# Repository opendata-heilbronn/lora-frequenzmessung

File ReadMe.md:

# LoRa Crowd Density Measurement

> Measure crowd density in public spaces using BLE scanning on ESP32 sensors, transmitted via LoRaWAN (TTN), stored in TimescaleDB, and visualised in a web UI and Grafana.

---

> **Canonical repository:** https://codeberg.org/cfhn/lora-frequenzmessung
>
> Mirrors exist on GitHub and GitLab for visibility, but they are read-only.
> **Contributions, issues, and pull requests belong on Codeberg.**

---

## Introduction

This project provides an end-to-end system for measuring crowd density in public spaces. Small ESP32-based sensors scan for nearby Bluetooth devices and transmit a count over LoRaWAN via The Things Network. A backend stack ingests the data and makes it available for real-time dashboards.

**Data flow:**

```
ESP32 (BLE scan)
    └─ LoRaWAN (TTN) ─→ MQTT Broker
                              └─ Aggregator ─→ Backend API ─→ TimescaleDB
                                                                    └─→ Grafana
                                                                    └─→ Web UI (via ManagementAPI)
```

**Maintained by** [Code for Heilbronn (CFHN)](https://codeforheilbronn.de/).

---

## Architecture

### Component Overview

| Service        | Language   | Port  | Purpose                                              |
|----------------|------------|-------|------------------------------------------------------|
| Backend        | Go/Fiber   | 3001  | Internal sensor CRUD + data ingestion (X-Internal-Key protected) |
| ManagementAPI  | Go/Fiber   | 3002  | Public API: JWT auth, TTN registration, firmware builds |
| Aggregator     | Go         | —     | MQTT subscriber → forwards data to Backend           |
| Frontend       | Vue 3/Vite | 5173  | Management web UI                                    |
| TimescaleDB    | PostgreSQL | 5432  | Time-series sensor data storage                      |
| Mosquitto      | MQTT       | 1883  | Message broker (TTN bridge)                          |
| Grafana        | —          | 3000  | Dashboard / visualisation                            |

### Request Paths

```
Browser  ──→  Frontend (Vite, :5173)
                  └─ /api/*  ──→  ManagementAPI (:3002)  ──→  Backend (:3001)
                  └─ /auth/* ──→  ManagementAPI (:3002)

TTN      ──→  MQTT (:1883)
                  └─  Aggregator  ──→  Backend (:3001)  ──→  TimescaleDB
```

<!-- Screenshots / diagrams can be added here once available -->

---

## Hardware Requirements

- **Heltec WiFi LoRa 32 V3** (ESP32-S3) — one per measurement location
- A LoRaWAN gateway in range
- A [The Things Network](https://www.thethingsnetwork.org/) application
- A server to run the backend stack (Docker + Docker Compose)

---

## Getting Started

### Prerequisites

| Tool | Version |
|------|---------|
| Go | 1.24+ |
| Node.js | 18+ |
| Docker & Docker Compose | latest |
| PlatformIO CLI | latest (for firmware builds) |
| `golang-migrate` | latest |

Install `golang-migrate` (macOS):

```bash
brew install golang-migrate
```

### Quick Start (Development)

```bash
# 1. Clone
git clone https://codeberg.org/cfhn/lora-frequenzmessung.git
cd lora-frequenzmessung

# 2. Configure environment
cp .env.local.dist backend/.env
# Edit backend/.env and fill in all required values (see Environment Variables below)

# 3. Start infrastructure (TimescaleDB, Mosquitto, Grafana)
make infra

# 4. Run database migrations
migrate -database "$DB_DSN" -path db/migrations up

# 5. Start all services in parallel
make dev
```

`make dev` starts the Backend (`:3001`), ManagementAPI (`:3002`), Aggregator, and Frontend (`:5173`) in parallel.

### Environment Variables

Copy `.env.local.dist` to `backend/.env` and fill in the required values.

| Variable | Required | Service(s) | Description |
|---|---|---|---|
| `DB_DSN` | Yes | Backend | PostgreSQL connection string |
| `INTERNAL_API_KEY` | Yes | Backend, ManagementAPI, Aggregator | Shared secret for internal service auth |
| `BACKEND_INTERNAL_URL` | Yes | ManagementAPI, Aggregator | URL of the internal Backend API (e.g. `http://localhost:3001`) |
| `JWT_SECRET` | Yes | ManagementAPI | HS256 signing key — min 32 characters |
| `ADMIN_USERNAME` | Yes | ManagementAPI | Admin login username |
| `ADMIN_PASSWORD` | Yes | ManagementAPI | Admin login password |
| `BROKER_HOST` | Yes | Aggregator | MQTT broker hostname |
| `BROKER_PORT` | Yes | Aggregator | MQTT broker port (usually `1883`) |
| `MQTT_USERNAME` | Yes | Aggregator | MQTT username (TTN app ID + `@ttn`) |
| `MQTT_PASSWORD` | Yes | Aggregator | MQTT API key from TTN |
| `TOPIC` | Yes | Aggregator | TTN MQTT topic to subscribe to |
| `TTN_APP_ID` | No | ManagementAPI | TTN application ID (for device provisioning) |
| `TTN_API_KEY` | No | ManagementAPI | TTN API key (for device provisioning) |
| `SENSOR_PAX_PATH` | No | ManagementAPI | Path to firmware source directory (default: `./sensor-pax`) |
| `CORS_ORIGINS` | No | ManagementAPI | Comma-separated allowed origins (e.g. `http://localhost:5173`) |

---

## Development Commands

All commands are run from the repository root via `make`. Run `make help` to see the full list.

```bash
make help              # Show all available targets

# Infrastructure
make infra             # Start TimescaleDB, Mosquitto, Grafana
make infra-down        # Stop infrastructure containers

# Backend services (each in its own terminal, or use make dev)
make backend           # Run internal Backend API (port 3001)
make management        # Run ManagementAPI (port 3002)
make aggregator        # Run MQTT Aggregator

# Frontend
make frontend          # Run Vite dev server (port 5173)

# All services at once
make dev               # Start infra + all services in parallel

# Testing
make test              # Run all Go tests
make test-frontend     # Run Playwright unit tests (mocked, no backend needed)
make test-frontend-live # Run Playwright integration tests (needs running backend)

# Build
make build             # Build all Go binaries + frontend bundle
```

---

## Testing

### Go Tests

```bash
cd backend
go test ./...
```

### Frontend — Playwright

There are two test projects configured in `frontend/playwright.config.ts`:

| Project | Command | Requires backend? |
|---|---|---|
| `unit` | `make test-frontend` | No (uses mocked API) |
| `integration` | `make test-frontend-live` | Yes (hits real backend) |

Run a single spec:

```bash
cd frontend
npx playwright test e2e/add-sensor.spec.ts
```

---

## Production Deployment

Docker images are published to `codeberg.org/cfhn/lora-frequenzmessung/<service>`.

Use `docker-compose-deploy.yml` to deploy the full stack:

```bash
docker compose -f docker-compose-deploy.yml up -d
```

All environment variables listed in the table above must be set in the production environment. For `POSTGRES_PASSWORD` and `GF_ADMIN_PASSWORD`, **change the defaults** — the development defaults (`password` / `admin`) are insecure.

---

## Project Structure

```
lora-frequenzmessung/
├── backend/               # All Go source code (single go.mod)
│   ├── Backend/           # Internal HTTP API (port 3001)
│   ├── ManagementAPI/     # Public JWT API (port 3002)
│   ├── Aggregator/        # MQTT subscriber
│   ├── structs/           # Shared Go types
│   └── internal/          # Shared internal packages
├── frontend/              # Vue 3 + Vite management UI
│   └── e2e/               # Playwright tests
├── sensor-pax/            # ESP32 firmware (PlatformIO / libpax)
├── db/
│   └── migrations/        # SQL migrations (golang-migrate)
├── docker/                # Dockerfiles + service configs
├── docs/                  # Additional documentation
├── hardware/              # Hardware schematics / notes
├── docker-compose.yml     # Development infrastructure
├── docker-compose-deploy.yml # Production deployment
└── Makefile               # Developer shortcuts
```

---

## Contributing

Contributions are welcome! This project is maintained by volunteers at [Code for Heilbronn (CFHN)](https://codeforheilbronn.de/).

**All contributions go through Codeberg:**

1. Fork the repository on [Codeberg](https://codeberg.org/cfhn/lora-frequenzmessung)
2. Create a feature branch (`git checkout -b feature/my-feature`)
3. Commit your changes following the existing code style
4. Open a pull request on Codeberg

Please open an issue first for larger changes so we can discuss the approach.

---

## License

MIT © 2026 [Open Data Heilbronn](https://codeforheilbronn.de/)

See [LICENSE](LICENSE) for the full text.

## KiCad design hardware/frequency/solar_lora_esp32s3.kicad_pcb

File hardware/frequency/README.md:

# Solar LoRa ESP32-S3 — Custom Slim Board

**Version:** 1.0
**Date:** 2026-02-15
**Band:** 868 MHz (EU)
**Based on:** Heltec WiFi LoRa 32 V3 (redesigned, no OLED)

---

## Overview

A slim, solar-powered LoRa development board built around the ESP32-S3-MINI-1
and Semtech SX1262. Designed for low-power outdoor sensor nodes.

**Board dimensions:** 22.0mm x 58.0mm (2-layer, 1.6mm thick, rounded corners)

## Key Features

- **ESP32-S3-MINI-1-N8** — WiFi + BLE, 8MB flash, native USB (no CH340 needed)
- **SX1262** — LoRa transceiver, 868 MHz, +22 dBm TX power, ultra-low sleep
- **CN3065** — Solar LiPo charger with Schottky diode OR from USB/solar
- **AP2112K-3.3** — 3.3V LDO, 600mA, ~55µA quiescent current
- **No OLED** — power saved for battery/solar operation
- **Battery monitoring** — voltage divider on ADC1 (GPIO1)
- **USB-C** — charging + native USB programming (no UART bridge chip)

## Pin Mapping (Software-Compatible with Heltec V3)

| Function      | ESP32-S3 GPIO | Notes                    |
|---------------|---------------|--------------------------|
| LoRa SCK      | GPIO8         | SPI clock                |
| LoRa MOSI     | GPIO9         | SPI data out             |
| LoRa MISO     | GPIO10        | SPI data in              |
| LoRa CS       | GPIO11        | SPI chip select          |
| LoRa RST      | GPIO12        | SX1262 reset             |
| LoRa BUSY     | GPIO13        | SX1262 busy flag         |
| LoRa DIO1     | GPIO14        | SX1262 interrupt         |
| USB D-        | GPIO19        | Native USB               |
| USB D+        | GPIO20        | Native USB               |
| Battery ADC   | GPIO1         | Via 100k/100k divider    |
| LED           | GPIO35        | User status LED (green)  |
| BOOT          | GPIO0         | Boot button (pull-up)    |
| RESET         | EN            | Reset button (pull-up)   |

## Power Architecture

```
USB-C (5V) ──D1 (SS14)──┐
                          ├── VOR ──► CN3065 ──► VBAT ──► AP2112K ──► +3V3
Solar (5-6V) ─D2 (SS14)─┘            │
                                ┌─────┘
                                │
                            JST-PH (LiPo 3.7V)
```

- **Solar panel recommendation:** 5V-6V, 500mA+ (e.g., 6V/1W mini panel)
- **Battery:** Single-cell LiPo, JST-PH 2-pin, 500mAh–2000mAh
- **Charge current:** Set by R1 (3kΩ → ~400mA). Adjust per CN3065 datasheet.
- **Charge indicator:** LED1 (red) on CHRG pin

## RF Design Notes (CRITICAL for 868 MHz performance)

The SX1262 RF section uses the Semtech AN1200.39 reference matching network:

```
SX1262 RFO ── C11 (1.0pF) ──┬── L2 (3.9nH) ── GND
                              │
                              ├── C12 (1.5pF) ── GND
                              │
                              └── SMA Antenna Connector
```

**Layout rules:**
1. RF trace from RFO to SMA MUST be 50Ω impedance matched
   - For standard 1.6mm FR4 (εr=4.5), use ~0.7mm trace on top layer with
     continuous ground plane beneath → microstrip ~50Ω
2. Keep RF traces as short as possible (< 15mm ideal)
3. NO vias in the RF signal path
4. Solid ground plane under entire SX1262 and RF section (back copper)
5. Multiple GND vias around SX1262 exposed pad
6. Place matching components (C11, L2, C12) directly adjacent to RFO pin
7. Keep >2mm clearance between RF trace and any other signal traces
8. SX1262 DC-DC inductor (L1, 15nH) must be close to VR_PA/VDD_IN pins

## TCXO

The 32 MHz TCXO (Y1) provides the reference clock for SX1262.
DIO3 of SX1262 can be configured in software to power the TCXO
(saves power in deep sleep). Connect TCXO VDD to SX1262 DIO3 output
if desired, or to +3V3 for always-on operation.

## How to Complete and Order

### Step 1: Open in KiCad 7+
- Open `solar_lora_esp32s3.kicad_pro`
- Review schematic (`.kicad_sch`) — check net connections
- Review PCB layout (`.kicad_pcb`) — components are placed but NOT routed

### Step 2: Route the PCB
- Use KiCad's interactive router (press 'X' to route)
- Route power traces first (+3V3, VBAT, GND) with wider widths (0.3-0.5mm)
- Route SPI bus (0.2mm traces, keep parallel, similar length)
- Route RF trace LAST — use 50Ω microstrip (see RF notes above)
- Fill ground zones (Edit → Fill All Zones, or press 'B')
- Run DRC (Inspect → Design Rules Check)

### Step 3: Generate Gerbers
- File → Fabrication Outputs → Gerbers
- Select layers: F.Cu, B.Cu, F.SilkS, B.SilkS, F.Mask, B.Mask, Edge.Cuts
- Also generate drill files (Excellon format)

### Step 4: Order from JLCPCB
- Go to jlcpcb.com → Order Now
- Upload Gerber ZIP
- Settings: 2-layer, 1.6mm, FR4, HASL lead-free
- For assembly: upload `BOM_JLCPCB.csv` and `CPL_JLCPCB.csv`
- Select "Economic PCBA" for cost savings
- Review component placement in the JLCPCB viewer

### Step 5: Verify LCSC Part Availability
Some parts (ESP32-S3-MINI-1, SX1262) may be "Extended" parts on JLCPCB
(extra $3 fee per unique extended part). Check availability before ordering.

## LCSC Part Alternatives

| Component | Primary LCSC | Alternative LCSC | Notes |
|-----------|-------------|-----------------|-------|
| ESP32-S3-MINI-1-N8 | C2913206 | C3013847 (N4 variant) | N4 = 4MB flash |
| SX1262IMLTRT | C125702 | C2843fault | Check stock |
| CN3065 | C82081 | C264872 | Same IC, different mfg |
| AP2112K-3.3 | C51118 | C166012 | Same specs |

## Low Power Tips

1. Use ESP32-S3 deep sleep (~7µA) between LoRa transmissions
2. Configure SX1262 sleep mode after TX/RX (~600nA)
3. TCXO powered by DIO3 (auto-off in sleep)
4. No OLED = ~15mA saved
5. AP2112K quiescent: ~55µA (consider ME6211 for ~40µA)
6. Total deep sleep: ~10-15µA (board level)
7. With 1000mAh battery + 6V/1W solar: indefinite outdoor operation

## Software

Compatible with:
- **Arduino IDE** — Use Heltec ESP32 board package, select "WiFi LoRa 32 V3"
- **PlatformIO** — board = `heltec_wifi_lora_32_V3`
- **ESP-IDF** — Target ESP32-S3, configure SPI pins manually
- **RadioLib** — SX1262 library, use pin definitions from table above

Example Arduino setup:
```cpp
#include <RadioLib.h>
SX1262 radio = new Module(11, 14, 12, 13); // CS, DIO1, RST, BUSY
// SPI: SCK=8, MOSI=9, MISO=10
```

## Development Setup

### Prerequisites

- Go 1.21+
- Node.js 18+
- Docker & Docker Compose
- [golang-migrate](https://github.com/golang-migrate/migrate) CLI

### Start Infrastructure

```bash
docker-compose up -d   # TimescaleDB, Mosquitto, Grafana
migrate -database "$DB_DSN" -path db/migrations up
```

### Start the Backend

```bash
cd backend
cp ../.env.local.dist .env.local   # adjust DB_DSN, TTN keys etc.
source .env.local
go run ./Backend
```

The API server starts on **port 3001**.

### Start the Frontend

```bash
cd frontend
npm install
npm run dev
```

The dev server starts on **port 5173** and proxies `/api/*` to the backend.

### Verify Tests

**Backend (Go):**

```bash
cd backend
go test ./...
```

**Frontend (Playwright — unit tests, no backend needed):**

```bash
cd frontend
npm install
npx playwright install --with-deps chromium
npx playwright test --project=unit
```

**Frontend (integration tests — requires running backend):**

```bash
npx playwright test --project=integration --workers=1
```

All 77 unit tests should pass. Integration tests create real sensors and need the backend + database running.

---
Generated by Solar LoRa PCB Generator | 2026-02-15

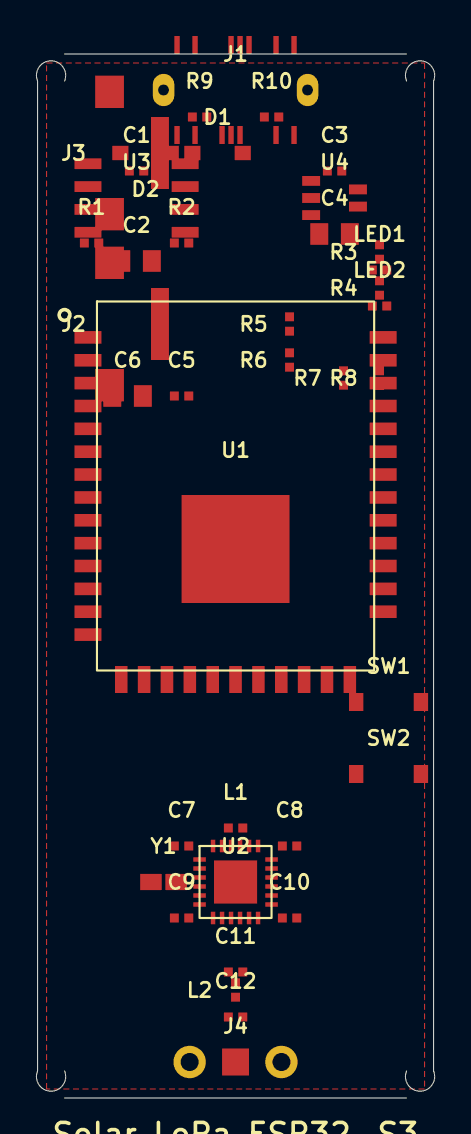
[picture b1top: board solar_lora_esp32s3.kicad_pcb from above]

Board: 2 copper layers, 22.1 x 58.0 mm, 39 parts (0 on the bottom side), 22 nets, no tracks yet.

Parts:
C1, C3, C5, C7, C8, C9: 100nF; R_0402
C2, C4, C6: 10uF; C_0805
C10: 47pF; R_0402
C11: 1.0pF; R_0402
C12: 1.5pF; R_0402
D1, D2: SS14; D_SOD-123
J1: USB-C; USB_C_Mid
J2: BATT; JST_PH_S2B
J3: SOLAR; JST_PH_S2B
J4: SMA; SMA_Edge
L1: 15nH; R_0402
L2: 3.9nH; R_0402
LED1: RED; R_0402
LED2: GREEN; R_0402
R1: 3k; R_0402
R2, R7, R8: 10k; R_0402
R3, R4: 1k; R_0402
R5, R6: 100k; R_0402
R9, R10: 5.1k; R_0402
SW1: RESET; SW_SPST_3x2.5
SW2: BOOT; SW_SPST_3x2.5
U1: ESP32-S3-MINI-1-N8; ESP32-S3-MINI-1
U2: SX1262; QFN-24-4x4
U3: CN3065; SOIC-8
U4: AP2112K-3.3; SOT-23-5
Y1: 32MHz; TCXO_2016

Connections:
+3V3: C4.1, C5.1, C6.1, C7.1, R7.1, R8.1, U1.2, U2.1, U4.5, Y1.1
BAT_ADC: R5.2, R6.1, U1.24
CHRG_STATUS: LED1.1, U3.7
EN: R7.2, SW1.1, U1.3
GND: C1.2, C2.2, C3.2, C4.2, C5.2, C6.2, C7.2, C8.2, C9.2, C12.2, J1.A1, J1.A12, J1.B1, J1.B12, J1.S1, J1.S2, J2.2, J3.2, J4.2, J4.3, L2.2, R1.2, R3.2, R4.2, R6.2, R9.2, R10.2, SW1.2, SW2.2, U1.1, U1.39, U2.2, U2.7, U2.8, U2.11, U2.14, U2.23, U2.24, U2.25, U3.2, U4.2
GPIO0: R8.2, SW2.1, U1.23
LED_GPIO: LED2.1, U1.33
LORA_BUSY: U1.21, U2.20
LORA_CS: U1.19, U2.18
LORA_DIO1: U1.22, U2.21
LORA_RST: U1.20, U2.19
RF_OUT: C11.1, J4.1, U2.13
SPI_MISO: U1.18, U2.16
SPI_MOSI: U1.17, U2.17
SPI_SCK: U1.12, U2.15
TCXO_OUT: U2.9, Y1.2
USB_DM: J1.A7, J1.B7, U1.13
USB_DP: J1.A6, J1.B6, U1.14
VBAT: C2.1, C3.1, C8.1, C9.1, J2.1, R5.1, U2.5, U2.6, U3.3, U4.1, U4.3
VBUS: D1.1, J1.A4, J1.A9, J1.B4, J1.B9
VOR: C1.1, D1.2, D2.1, U3.5
VSOLAR: D2.2, J3.1

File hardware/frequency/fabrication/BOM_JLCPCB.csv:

Comment,Designator,Footprint,LCSC Part #
ESP32-S3-MINI-1-N8,U1,ESP32-S3-MINI-1,C2913206
SX1262IMLTRT,U2,QFN-24-4x4,C125702
CN3065,U3,SOIC-8,C82081
AP2112K-3.3TRG1,U4,SOT-23-5,C51118
USB-C-2.0,J1,USB_C_Mid,C168688
JST-PH-2P,J2,JST_PH_S2B,C131337
JST-PH-2P,J3,JST_PH_S2B,C131337
SMA-Edge,J4,SMA_Edge,C496549
RESET,SW1,SW_3x2.5,C318884
BOOT,SW2,SW_3x2.5,C318884
SS14,D1,SOD-123,C8598
SS14,D2,SOD-123,C8598
RED,LED1,LED_0402,C2286
GREEN,LED2,LED_0402,C2297
3k,R1,R_0402,C25890
10k,R2,R_0402,C25744
1k,R3,R_0402,C11702
1k,R4,R_0402,C11702
100k,R5,R_0402,C25741
100k,R6,R_0402,C25741
10k,R7,R_0402,C25744
10k,R8,R_0402,C25744
5.1k,R9,R_0402,C25905
5.1k,R10,R_0402,C25905
100nF,C1,C_0402,C1525
10uF,C2,C_0805,C15850
100nF,C3,C_0402,C1525
10uF,C4,C_0805,C15850
100nF,C5,C_0402,C1525
10uF,C6,C_0805,C15850
100nF,C7,C_0402,C1525
100nF,C8,C_0402,C1525
100nF,C9,C_0402,C1525
47pF,C10,C_0402,C1554
1.0pF,C11,C_0402,C52726
1.5pF,C12,C_0402,C52727
15nH,L1,L_0402,C76977
3.9nH,L2,L_0402,C76613
32MHz,Y1,TCXO_2016,C2838573

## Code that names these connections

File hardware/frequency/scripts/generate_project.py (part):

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    ("SW1", "RESET", "SW_3x2.5", "C318884",
     "Tactile switch reset", 20.0, 36.0, 0),
    ("SW2", "BOOT", "SW_3x2.5", "C318884",
     "Tactile switch boot/GPIO0", 20.0, 40.0, 0),
    ("D1", "SS14", "SOD-123", "C8598",
     "Schottky diode USB VBUS", 8.0, 5.5, 0),
    ("D2", "SS14", "SOD-123", "C8598",
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    ("R7", "10k", "R_0402", "C25744",
     "EN pull-up", 17.0, 18.0, 90),
    ("R8", "10k", "R_0402", "C25744",
     "GPIO0 pull-up", 19.0, 18.0, 90),
    # USB-C CC resistors
    ("R9", "5.1k", "R_0402", "C25905",
     "USB CC1 pull-down", 9.0, 3.0, 0),
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    (14, "USB_DP"),
    (15, "USB_DM"),
    (16, "BAT_ADC"),
    (17, "LED_GPIO"),
    (18, "CHRG_STATUS"),
    (19, "RF_OUT"),
    (20, "TCXO_OUT"),
    (21, "EN"),
    (22, "GPIO0"),
]

# ════════════════════════════════════════════════════════════
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    # ── MCU Section (x=200..280, y=30..100) ──
    place_symbol("ESP32-S3-MINI-1", "U1", "ESP32-S3-MINI-1", 240, 65)
    place_symbol("R", "R7", "10k", 215, 35, props={"Description": "EN pull-up"})
    place_symbol("R", "R8", "10k", 230, 100, props={"Description": "GPIO0 pull-up"})
    place_symbol("SW_Push", "SW1", "RESET", 210, 40)
    place_symbol("SW_Push", "SW2", "BOOT", 225, 105)
    place_symbol("C", "C5", "100nF", 220, 30)
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
    # Key net labels
    add_label("VBUS", 75, 42)
    add_label("VSOLAR", 75, 58)
    add_label("VOR", 95, 50)
    add_label("VBAT", 125, 50)
    add_label("+3V3", 175, 50)
    add_label("GND", 110, 60)
    add_label("SPI_SCK", 270, 55)
    add_label("SPI_MOSI", 270, 58)
    add_label("SPI_MISO", 270, 61)
    add_label("LORA_CS", 270, 64)
    add_label("LORA_RST", 270, 67)
    add_label("LORA_BUSY", 270, 70)
    add_label("LORA_DIO1", 270, 73)
    add_label("USB_DP", 55, 47)
    add_label("USB_DM", 55, 50)
    add_label("BAT_ADC", 135, 100)
    add_label("RF_OUT", 360, 80)
    add_label("EN", 215, 40)
    add_label("GPIO0", 225, 100)

    # ── Write all to schematic ──
    for inst in instances:
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            (20, "IO12",   11, "LORA_RST"),
            (21, "IO13",   12, "LORA_BUSY"),
            (22, "IO14",   13, "LORA_DIO1"),
            (23, "IO0",    22, "GPIO0"),
            (24, "IO1",    16, "BAT_ADC"),
            (25, "IO2",    0, ""),
        ]
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            (30, "IO38",   0, ""),
            (31, "IO37",   0, ""),
            (32, "IO36",   0, ""),
            (33, "IO35",   17, "LED_GPIO"),
            (34, "IO34",   0, ""),
            (35, "IO33",   0, ""),
            (36, "IO26",   0, ""),
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    pcb.append(place_switch("SW1", "RESET", 19.5, 36.0, 0,
                             net1=(21, "EN"), net2=(1, "GND")))
    pcb.append(place_switch("SW2", "BOOT", 19.5, 40.0, 0,
                             net1=(22, "GPIO0"), net2=(1, "GND")))

    # Schottky diodes
    pcb.append(place_sod123("D1", "SS14", 10.0, 5.5, 0,
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    pcb.append(place_0402("LED1", "RED", 19.0, 12.0, 0,
                           net1=(18, "CHRG_STATUS"), net2=(0, "")))
    pcb.append(place_0402("LED2", "GREEN", 19.0, 14.0, 0,
                           net1=(17, "LED_GPIO"), net2=(0, "")))

    # Resistors
    pcb.append(place_0402("R1", "3k",    3.0, 10.5, 0, net1=(0,""), net2=(1,"GND")))  # ISET
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    pcb.append(place_0402("R5", "100k",  14.0, 15.0, 90, net1=(6,"VBAT"), net2=(16,"BAT_ADC")))
    pcb.append(place_0402("R6", "100k",  14.0, 17.0, 90, net1=(16,"BAT_ADC"), net2=(1,"GND")))
    pcb.append(place_0402("R7", "10k",   17.0, 18.0, 90, net1=(2,"+3V3"), net2=(21,"EN")))
    pcb.append(place_0402("R8", "10k",   19.0, 18.0, 90, net1=(2,"+3V3"), net2=(22,"GPIO0")))
    pcb.append(place_0402("R9", "5.1k",  9.0,  3.5, 0, net2=(1,"GND")))  # CC1
    pcb.append(place_0402("R10","5.1k",  13.0, 3.5, 0, net2=(1,"GND")))  # CC2

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    svg += wire(160, 246, 180, 246)
    svg += wire(180, 111, 180, 246, "#c00")
    svg += f'<circle cx="180" cy="178" r="3" fill="#c00"/>\n'
    svg += label(183, 175, "VOR", 10, "#c00")

    # CN3065
    svg += box(200, 120, 120, 140, "U3: CN3065",
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    svg += wire(375, 195, 375, 205, "#888")
    svg += wire(375, 215, 375, 225, "#888")
    svg += wire(375, 235, 375, 245, "#888")
    svg += label(380, 222, "BAT_ADC →", 8, "#060")
    svg += label(380, 248, "GND", 8, "#666")

    # AP2112K LDO
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    svg += label(470, 72, "── MCU ──", 12, "#006")

    esp_pins_l = [
        ("3V3", "+3V3"), ("EN", "EN"), ("IO0/BOOT", "GPIO0"),
        ("IO1/ADC", "BAT_ADC"), ("IO8/SCK", "SPI_SCK"), ("IO9/MOSI", "SPI_MOSI"),
        ("IO10/MISO", "SPI_MISO"), ("IO11/CS", "LORA_CS"),
    ]
    esp_pins_r = [
        ("IO19/D-", "USB_DM"), ("IO20/D+", "USB_DP"),
        ("IO12/RST_L", "LORA_RST"), ("IO13/BUSY", "LORA_BUSY"),
        ("IO14/DIO1", "LORA_DIO1"), ("IO35/LED", "LED_GPIO"),
        ("GND", "GND"), ("IO4..IO7", "GPIO"),
    ]
    svg += box(470, 85, 200, 300, "U1: ESP32-S3-MINI-1-N8",
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    svg += box(380, 110, 70, 35, "SW1: RESET",
               [("1", "EN")], [("2", "GND")], "#f8f0f0")
    svg += box(380, 150, 70, 35, "SW2: BOOT",
               [("1", "GPIO0")], [("2", "GND")], "#f8f0f0")

    # LED
    svg += label(690, 300, "LED2: GREEN", 8, "#080")
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    | USB D+        | GPIO20        | Native USB               |
    | Battery ADC   | GPIO1         | Via 100k/100k divider    |
    | LED           | GPIO35        | User status LED (green)  |
    | BOOT          | GPIO0         | Boot button (pull-up)    |
    | RESET         | EN            | Reset button (pull-up)   |

    ## Power Architecture
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        ],
        "VBUS": ["J1.VBUS", "D1.A (anode)"],
        "VSOLAR": ["J3.1", "D2.A (anode)"],
        "VOR": ["D1.K (cathode)", "D2.K (cathode)", "U3.VIN (pin5)", "C1.1"],
        "VBAT": [
            "U3.BAT (pin3)", "J2.1",
            "U4.VIN (pin1)", "U4.EN (pin3)",
            "R5.1", "C2.1", "C3.1",
            "U2.VBAT (pin5)", "U2.VBAT_IO (pin6)", "C8.1", "C9.1",
        ],
        "SPI_SCK":  ["U1.IO8 (pin12)", "U2.SCK (pin15)"],
        "SPI_MOSI": ["U1.IO9 (pin17)", "U2.MOSI (pin17)"],
        "SPI_MISO": ["U1.IO10 (pin18)", "U2.MISO (pin16)"],
        "LORA_CS":  ["U1.IO11 (pin19)", "U2.NSS (pin18)"],
        "LORA_RST": ["U1.IO12 (pin20)", "U2.NRESET (pin19)"],
        "LORA_BUSY":["U1.IO13 (pin21)", "U2.BUSY (pin20)"],
        "LORA_DIO1":["U1.IO14 (pin22)", "U2.DIO1 (pin21)"],
        "USB_DP":   ["J1.D+", "U1.IO20 (pin14)"],
        "USB_DM":   ["J1.D-", "U1.IO19 (pin13)"],
        "BAT_ADC":  ["R5.2", "R6.1", "U1.IO1 (pin24)"],
        "LED_GPIO": ["U1.IO35 (pin33)", "LED2.A"],
        "CHRG_STATUS": ["U3.CHRG (pin7)", "LED1.A"],
        "RF_OUT":   ["U2.RFO (pin13)", "C11.1"],
        "TCXO_OUT": ["Y1.OUT", "U2.XTA (pin9)"],
        "EN":       ["R7.2", "U1.EN (pin3)", "SW1.1"],
        "GPIO0":    ["R8.2", "U1.IO0 (pin23)", "SW2.1"],
    }

    lines = ["NETLIST — Solar LoRa ESP32-S3\n" + "="*50 + "\n"]
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
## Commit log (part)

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2025-01-23 general information
2025-01-30 added infra
2025-02-06 added demo data
2025-02-06 added demo data sending and agregator config loader
2025-02-20 added aggreator
2025-02-23 added backend
2025-02-27 added env loader
2025-03-04 add some code of sensor
2025-03-06 moved backend code
2025-03-08 added open api yml
2025-03-08 clean up
2025-03-08 added dot env
2025-03-08 added
2025-03-08 docker file update
2025-03-08 fixed agregator ?
2025-03-13 fix docker file backend
2025-03-13 update logging
2025-03-13 added new env var BACKEND_URL
2025-03-13 fixed db innsert
2025-03-13 debugging messages
2025-03-27 added test
2025-07-23 some cleanup
2025-08-07 switch libpax lib dir name
2025-08-08 ignore ds store files
2025-08-28 add make fair changes
2025-08-28 added faktor and debung display
2025-08-28 added hard fail if mqqt fails
2025-09-11 deployed
2025-09-11 [#0] changed waydata is send
2025-09-25 added lora function
2025-09-25 added new client
2025-09-25 WORKS
2025-09-30 works with battery
2025-09-30 added logging functionality and integrated it across the project
2025-10-09 updated LoRa duty cycle calculation, fixed battery ADC pin, and adjusted power control logic
2025-10-16 Add new client entry for maker-space-01
2026-02-15 added bet lora sensore files
2026-02-16 WIP mesh
2026-02-18 added WIP frontent
2026-02-19 added wip PCB
2026-02-25 new sensore :)
2026-02-25 added Firmeware
2026-02-25 added ota
2026-02-25 fixed pipline
2026-02-27 fixed battery bug
2026-02-27 added new better frontend
2026-02-27 made sensore waaaay smaller
2026-02-27 frontent can now add sensore wich work
2026-02-27 feixed test
2026-02-27 added new deploment setup
2026-02-28 cleanup
2026-02-28 added e2e pipline
2026-02-28 added CI piplines
2026-02-28 fixed naming of CIs
2026-02-28 [#0]
2026-02-28 added deploy piplines
2026-02-28 removed old github CI
2026-02-28 reworked file structore for deployment piplines
2026-02-28 fixed bug in piplines
2026-03-01 added new deployment workflow
2026-03-01 changed the container path to point to codeberg
2026-03-01 changed tag of docker image for codeberg
2026-03-01 deployment
2026-03-01 added migrations
2026-03-01 fixed ci bug and also some deployment stuff
2026-03-01 fixed env bug
2026-03-01 fixed typo in test
2026-03-01 fixed cors errors
2026-03-01 feat(map): add locate me button to MapPicker
    Adds a ⊕ button overlaid on the map that centers the marker on the
    user's current GPS position via the browser Geolocation API. Shows a
    spinner while fetching and surfaces an error tooltip if access is denied.
    Includes two Playwright tests covering button visibility and coordinate
    update behavior with a mocked geolocation.
2026-03-01 boyscoure
2026-03-01 added firware setup
2026-03-01 fixed bug with version system
2026-03-01 UI improvements
2026-03-01 fixed tests for ui impovments
2026-03-01 OTA POC
2026-03-08 next try depencie scanner
2026-03-09 fixed sonar qube connection
2026-03-09 fixed frontend ci workflow
2026-03-13 Add daily PostgreSQL backup service to docker-compose-deploy configuration
2026-03-29 Authentication (#42)
    - Add database for the management API to store user information in
    - Move OnyxPageLayout into individual views, so the LoginView can be without padding
    - Modify login endpoint to authenticate against a user table with argon2id hashes
    - Reduce authentication token lifetime and introduce refresh token as httponly secure cookie
    - Clamp max session lifetime on refresh token to 7 days
    - Add refresh endpoint that returns a new token if a valid refresh token is passed via cookie
2026-04-16 oush emergy fixes
2026-05-01 added reset PW
2026-05-31 Refactoring and Linting (#51)
    most packages are now named with lowercase and applied linting for most files. still lots of work todo to get things the right way but not to block everything, i want to have this merged and go packa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
    Reviewed-on: https://codeberg.org/cfhn/lorax/pulls/51
2026-06-18 fix this (#52)
    Reviewed-on: https://codeberg.org/cfhn/lorax/pulls/52
    Reviewed-by: hmnd <hmnd@noreply.codeberg.org>

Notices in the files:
ReadMe.md:
MIT License
